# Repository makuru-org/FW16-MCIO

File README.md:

<!--
# Usecase
This is the source files needed to easily create an Framework 16 to MCIO expansion bay, so one can add a external GPU to the FW 16.
# PCB Render

# Schematics

# How to use
1. Order PCB by JLCPCB with the correct impedence matching. (pls create issue if confused or help needed)
2. Order ADT-link's MCIO to PCIe eGPU station with MCIO cable. (tested with F37C version)
3. Print repo's STD files with a 3D printer.

# License
My changes are licensed under: [https://cern-ohl.web.cern.ch/](CERN-OHL-S).

The plain PCB template is I believe the https://github.com/jyancat/ExpansionBay under CC BY 4.0.

This is a fork of the [https://github.com/Terrails/FW16-OCuLink](Terrails), work as of writting this, it is not licensed, IE under **UNLICENSED**.
--!>
# STILL IN DEV

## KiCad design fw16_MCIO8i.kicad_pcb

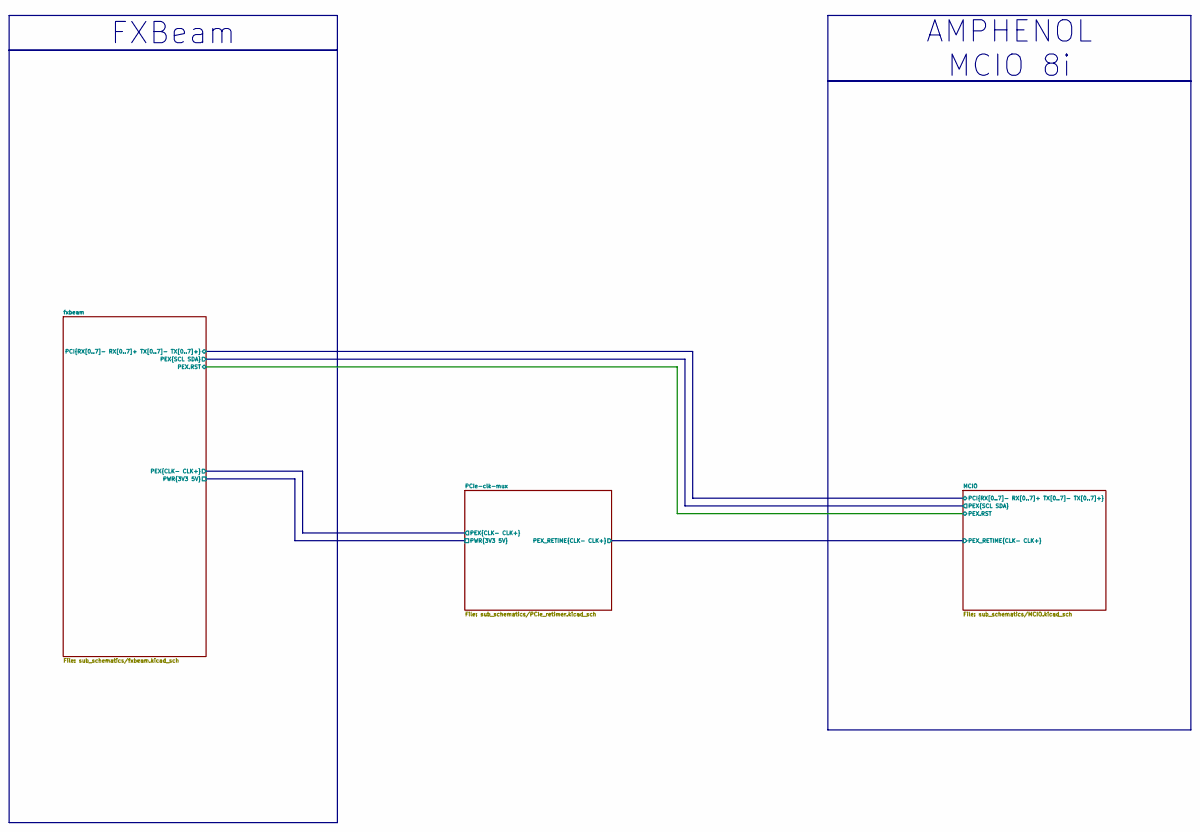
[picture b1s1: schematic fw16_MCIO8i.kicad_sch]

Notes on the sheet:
AMPHENOL MCIO 8i
FXBeam

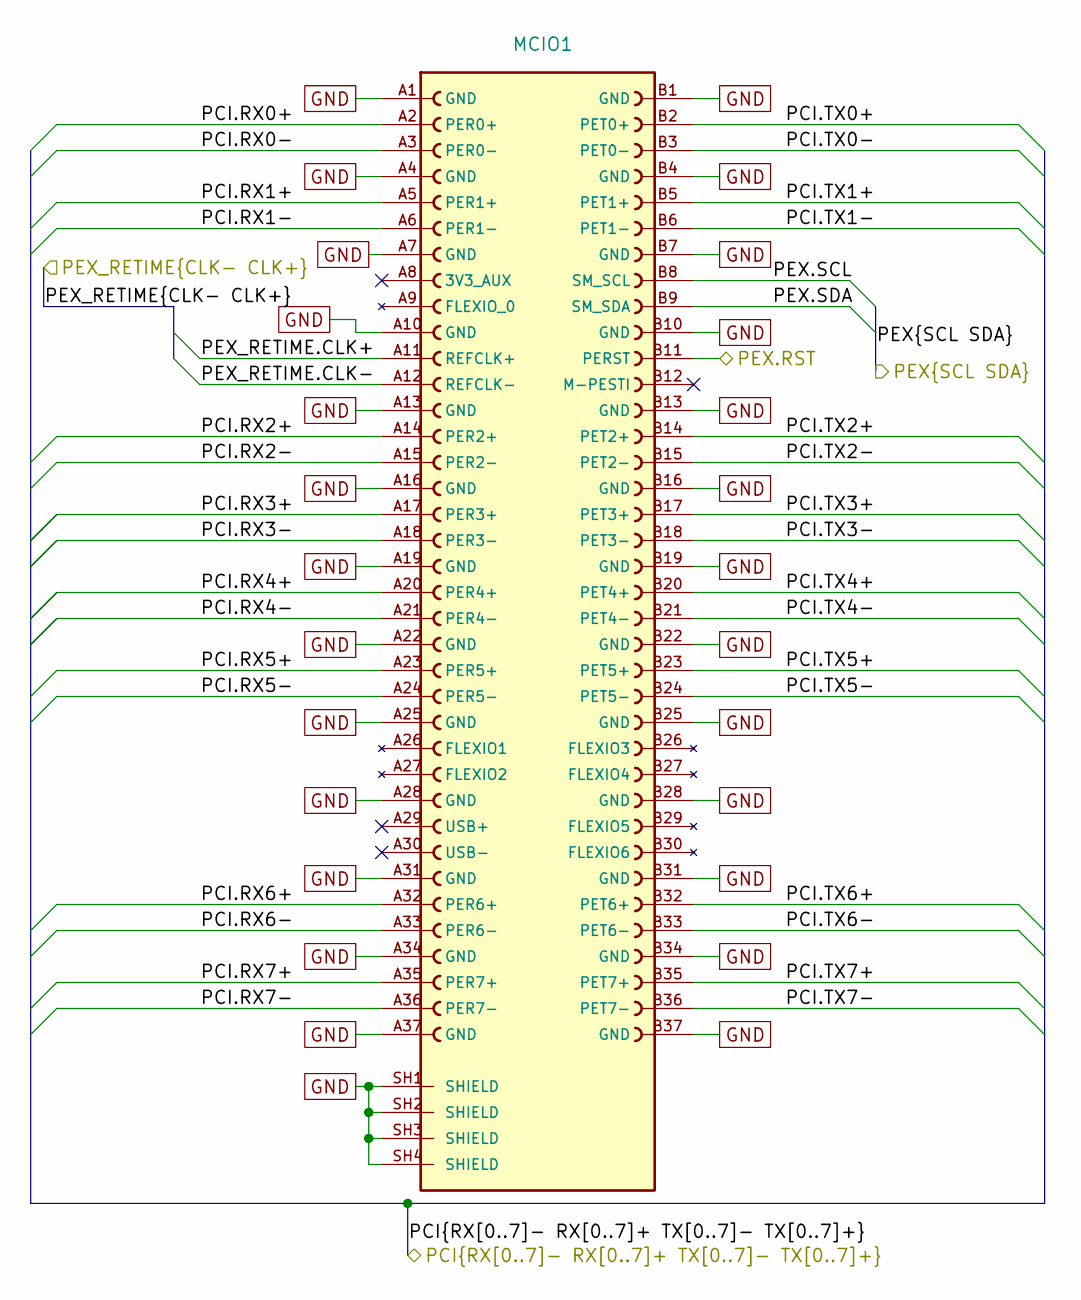
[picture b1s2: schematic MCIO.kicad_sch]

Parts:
MCIO1: G97R22312HR; AMPHENOL_G97R22312HR; PARTREV AX16; JLCPCB Part # C4499806

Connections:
/MCIO/PCI.RX0+: MCIO1.A2 (PER0+); also elsewhere on the board
/MCIO/PCI.RX0-: MCIO1.A3 (PER0-); also elsewhere on the board
/MCIO/PCI.RX1+: MCIO1.A5 (PER1+); also elsewhere on the board
/MCIO/PCI.RX1-: MCIO1.A6 (PER1-); also elsewhere on the board
/MCIO/PCI.RX2+: MCIO1.A14 (PER2+); also elsewhere on the board
/MCIO/PCI.RX2-: MCIO1.A15 (PER2-); also elsewhere on the board
/MCIO/PCI.RX3+: MCIO1.A17 (PER3+); also elsewhere on the board
/MCIO/PCI.RX3-: MCIO1.A18 (PER3-); also elsewhere on the board
/MCIO/PCI.RX4+: MCIO1.A20 (PER4+); also elsewhere on the board
/MCIO/PCI.RX4-: MCIO1.A21 (PER4-); also elsewhere on the board
/MCIO/PCI.RX5+: MCIO1.A23 (PER5+); also elsewhere on the board
/MCIO/PCI.RX5-: MCIO1.A24 (PER5-); also elsewhere on the board
/MCIO/PCI.RX6+: MCIO1.A32 (PER6+); also elsewhere on the board
/MCIO/PCI.RX6-: MCIO1.A33 (PER6-); also elsewhere on the board
/MCIO/PCI.RX7+: MCIO1.A35 (PER7+); also elsewhere on the board
/MCIO/PCI.RX7-: MCIO1.A36 (PER7-); also elsewhere on the board
/MCIO/PCI.TX0+: MCIO1.B2 (PET0+); also elsewhere on the board
/MCIO/PCI.TX0-: MCIO1.B3 (PET0-); also elsewhere on the board
/MCIO/PCI.TX1+: MCIO1.B5 (PET1+); also elsewhere on the board
/MCIO/PCI.TX1-: MCIO1.B6 (PET1-); also elsewhere on the board
/MCIO/PCI.TX2+: MCIO1.B14 (PET2+); also elsewhere on the board
/MCIO/PCI.TX2-: MCIO1.B15 (PET2-); also elsewhere on the board
/MCIO/PCI.TX3+: MCIO1.B17 (PET3+); also elsewhere on the board
/MCIO/PCI.TX3-: MCIO1.B18 (PET3-); also elsewhere on the board
/MCIO/PCI.TX4+: MCIO1.B20 (PET4+); also elsewhere on the board
/MCIO/PCI.TX4-: MCIO1.B21 (PET4-); also elsewhere on the board
/MCIO/PCI.TX5+: MCIO1.B23 (PET5+); also elsewhere on the board
/MCIO/PCI.TX5-: MCIO1.B24 (PET5-); also elsewhere on the board
/MCIO/PCI.TX6+: MCIO1.B32 (PET6+); also elsewhere on the board
/MCIO/PCI.TX6-: MCIO1.B33 (PET6-); also elsewhere on the board
/MCIO/PCI.TX7+: MCIO1.B35 (PET7+); also elsewhere on the board
/MCIO/PCI.TX7-: MCIO1.B36 (PET7-); also elsewhere on the board
/MCIO/PEX.SCL: MCIO1.B8 (SM_SCL); also elsewhere on the board
/MCIO/PEX.SDA: MCIO1.B9 (SM_SDA); also elsewhere on the board
/MCIO/PEX_RETIME.CLK+: MCIO1.A11 (REFCLK+); also elsewhere on the board
/MCIO/PEX_RETIME.CLK-: MCIO1.A12 (REFCLK-); also elsewhere on the board
/fxbeam/PEX.RST: MCIO1.B11 (PERST); also elsewhere on the board
GND: MCIO1.A1 (GND), MCIO1.A4 (GND), MCIO1.A7 (GND), MCIO1.A10 (GND), MCIO1.A13 (GND), MCIO1.A16 (GND), MCIO1.A19 (GND), MCIO1.A22 (GND), MCIO1.A25 (GND), MCIO1.A28 (GND), MCIO1.A31 (GND), MCIO1.A34 (GND), MCIO1.A37 (GND), MCIO1.B1 (GND), MCIO1.B4 (GND), MCIO1.B7 (GND), MCIO1.B10 (GND), MCIO1.B13 (GND), MCIO1.B16 (GND), MCIO1.B19 (GND), MCIO1.B22 (GND), MCIO1.B25 (GND), MCIO1.B28 (GND), MCIO1.B31 (GND), MCIO1.B34 (GND), MCIO1.B37 (GND), MCIO1.SH1 (SHIELD), MCIO1.SH2 (SHIELD), MCIO1.SH3 (SHIELD), MCIO1.SH4 (SHIELD); also elsewhere on the board

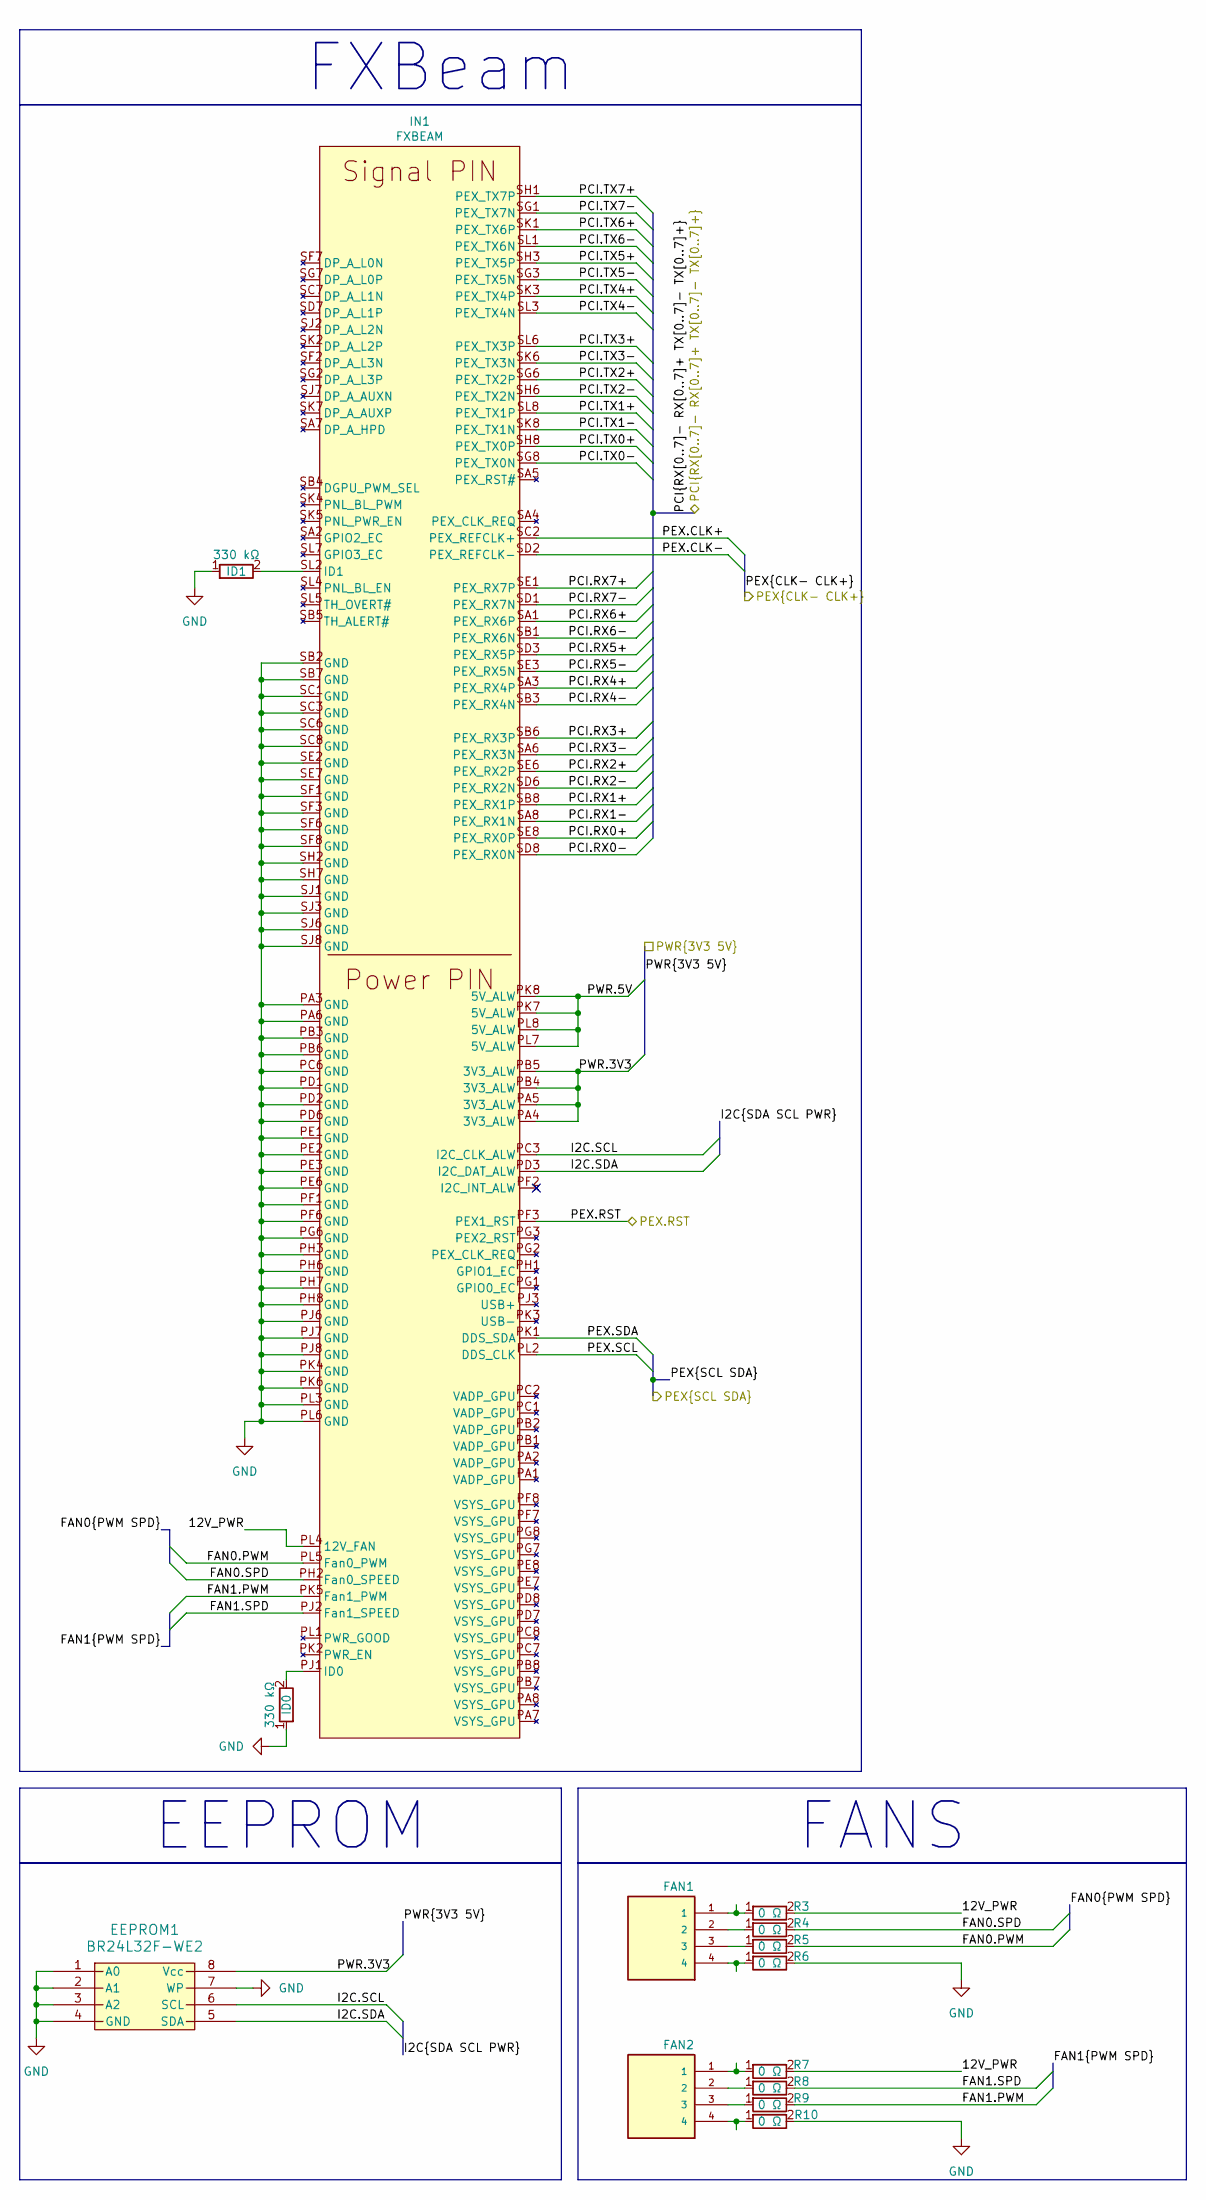
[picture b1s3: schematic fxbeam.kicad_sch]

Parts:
EEPROM1: BR24L32F-WE2; SOP8_ROM; MPN BR24L32F-WE2; JLCPCB Part # C253183
FAN1, FAN2: F3311A7H121004E200; AMPHENOL_F3311A7H121004E200; PARTREV A; JLCPCB Part # C3169422
ID0, ID1: 1206_R_560112132036; R_Wurth_WRIS-RSKS-1206_W; Part Number 560112132036; JLCPCB Part # C26798316
IN1: FXBEAM
R3, R4, R5, R6, R7, R8, R9, R10: 1206_R_560112132007; R_Wurth_WRIS-RSKS-1206_W; Part Number 560112132007; JLCPCB Part # C25268462

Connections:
/MCIO/PCI.RX0+: IN1.SE8 (PEX_RX0P); also elsewhere on the board
/MCIO/PCI.RX0-: IN1.SD8 (PEX_RX0N); also elsewhere on the board
/MCIO/PCI.RX1+: IN1.SB8 (PEX_RX1P); also elsewhere on the board
/MCIO/PCI.RX1-: IN1.SA8 (PEX_RX1N); also elsewhere on the board
/MCIO/PCI.RX2+: IN1.SE6 (PEX_RX2P); also elsewhere on the board
/MCIO/PCI.RX2-: IN1.SD6 (PEX_RX2N); also elsewhere on the board
/MCIO/PCI.RX3+: IN1.SB6 (PEX_RX3P); also elsewhere on the board
/MCIO/PCI.RX3-: IN1.SA6 (PEX_RX3N); also elsewhere on the board
/MCIO/PCI.RX4+: IN1.SA3 (PEX_RX4P); also elsewhere on the board
/MCIO/PCI.RX4-: IN1.SB3 (PEX_RX4N); also elsewhere on the board
/MCIO/PCI.RX5+: IN1.SD3 (PEX_RX5P); also elsewhere on the board
/MCIO/PCI.RX5-: IN1.SE3 (PEX_RX5N); also elsewhere on the board
/MCIO/PCI.RX6+: IN1.SA1 (PEX_RX6P); also elsewhere on the board
/MCIO/PCI.RX6-: IN1.SB1 (PEX_RX6N); also elsewhere on the board
/MCIO/PCI.RX7+: IN1.SE1 (PEX_RX7P); also elsewhere on the board
/MCIO/PCI.RX7-: IN1.SD1 (PEX_RX7N); also elsewhere on the board
/MCIO/PCI.TX0+: IN1.SH8 (PEX_TX0P); also elsewhere on the board
/MCIO/PCI.TX0-: IN1.SG8 (PEX_TX0N); also elsewhere on the board
/MCIO/PCI.TX1+: IN1.SL8 (PEX_TX1P); also elsewhere on the board
/MCIO/PCI.TX1-: IN1.SK8 (PEX_TX1N); also elsewhere on the board
/MCIO/PCI.TX2+: IN1.SG6 (PEX_TX2P); also elsewhere on the board
/MCIO/PCI.TX2-: IN1.SH6 (PEX_TX2N); also elsewhere on the board
/MCIO/PCI.TX3+: IN1.SL6 (PEX_TX3P); also elsewhere on the board
/MCIO/PCI.TX3-: IN1.SK6 (PEX_TX3N); also elsewhere on the board
/MCIO/PCI.TX4+: IN1.SK3 (PEX_TX4P); also elsewhere on the board
/MCIO/PCI.TX4-: IN1.SL3 (PEX_TX4N); also elsewhere on the board
/MCIO/PCI.TX5+: IN1.SH3 (PEX_TX5P); also elsewhere on the board
/MCIO/PCI.TX5-: IN1.SG3 (PEX_TX5N); also elsewhere on the board
/MCIO/PCI.TX6+: IN1.SK1 (PEX_TX6P); also elsewhere on the board
/MCIO/PCI.TX6-: IN1.SL1 (PEX_TX6N); also elsewhere on the board
/MCIO/PCI.TX7+: IN1.SH1 (PEX_TX7P); also elsewhere on the board
/MCIO/PCI.TX7-: IN1.SG1 (PEX_TX7N); also elsewhere on the board
/MCIO/PEX.SCL: IN1.PL2 (DDS_CLK); also elsewhere on the board
/MCIO/PEX.SDA: IN1.PK1 (DDS_SDA); also elsewhere on the board
/PCIe-clk-mux/PEX.CLK+: IN1.SC2 (PEX_REFCLK+); also elsewhere on the board
/PCIe-clk-mux/PEX.CLK-: IN1.SD2 (PEX_REFCLK-); also elsewhere on the board
/PCIe-clk-mux/PWR.3V3: EEPROM1.8 (Vcc), IN1.PA4 (3V3_ALW), IN1.PA5 (3V3_ALW), IN1.PB4 (3V3_ALW), IN1.PB5 (3V3_ALW); also elsewhere on the board
/PCIe-clk-mux/PWR.5V: IN1.PK7 (5V_ALW), IN1.PK8 (5V_ALW), IN1.PL7 (5V_ALW), IN1.PL8 (5V_ALW)
/fxbeam/12V_PWR: IN1.PL4 (12V_FAN), R3.2, R7.2
/fxbeam/FAN0.PWM: IN1.PL5 (Fan0_PWM), R5.2
/fxbeam/FAN0.SPD: IN1.PH2 (Fan0_SPEED), R4.2
/fxbeam/FAN1.PWM: IN1.PK5 (Fan1_PWM), R9.2
/fxbeam/FAN1.SPD: IN1.PJ2 (Fan1_SPEED), R8.2
/fxbeam/I2C.SCL: EEPROM1.6 (SCL), IN1.PC3 (I2C_CLK_ALW)
/fxbeam/I2C.SDA: EEPROM1.5 (SDA), IN1.PD3 (I2C_DAT_ALW)
/fxbeam/PEX.RST: IN1.PF3 (PEX1_RST); also elsewhere on the board
GND: EEPROM1.1 (A0), EEPROM1.2 (A1), EEPROM1.3 (A2), EEPROM1.4 (GND), EEPROM1.7 (WP), ID0.1, ID1.1, IN1.PA3 (GND), IN1.PA6 (GND), IN1.PB3 (GND), IN1.PB6 (GND), IN1.PC6 (GND), IN1.PD1 (GND), IN1.PD2 (GND), IN1.PD6 (GND), IN1.PE1 (GND), IN1.PE2 (GND), IN1.PE3 (GND), IN1.PE6 (GND), IN1.PF1 (GND), IN1.PF6 (GND), IN1.PG6 (GND), IN1.PH3 (GND), IN1.PH6 (GND), IN1.PH7 (GND), IN1.PH8 (GND), IN1.PJ6 (GND), IN1.PJ7 (GND), IN1.PJ8 (GND), IN1.PK4 (GND), IN1.PK6 (GND), IN1.PL3 (GND), IN1.PL6 (GND), IN1.SB2 (GND), IN1.SB7 (GND), IN1.SC1 (GND), IN1.SC3 (GND), IN1.SC6 (GND), IN1.SC8 (GND), IN1.SE2 (GND), IN1.SE7 (GND), IN1.SF1 (GND), IN1.SF3 (GND), IN1.SF6 (GND), IN1.SF8 (GND), IN1.SH2 (GND), IN1.SH7 (GND), IN1.SJ1 (GND), IN1.SJ3 (GND), IN1.SJ6 (GND), IN1.SJ8 (GND), R6.2, R10.2; also elsewhere on the board
unnamed: FAN1.1, R3.1
unnamed: FAN1.2, R4.1
unnamed: FAN1.3, R5.1
unnamed: FAN1.4, R6.1
unnamed: FAN2.1, R7.1
unnamed: FAN2.2, R8.1
unnamed: FAN2.3, R9.1
unnamed: FAN2.4, R10.1
unnamed: ID0.2, IN1.PJ1 (ID0)
unnamed: ID1.2, IN1.SL2 (ID1)

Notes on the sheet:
EEPROM
FANS
FXBeam

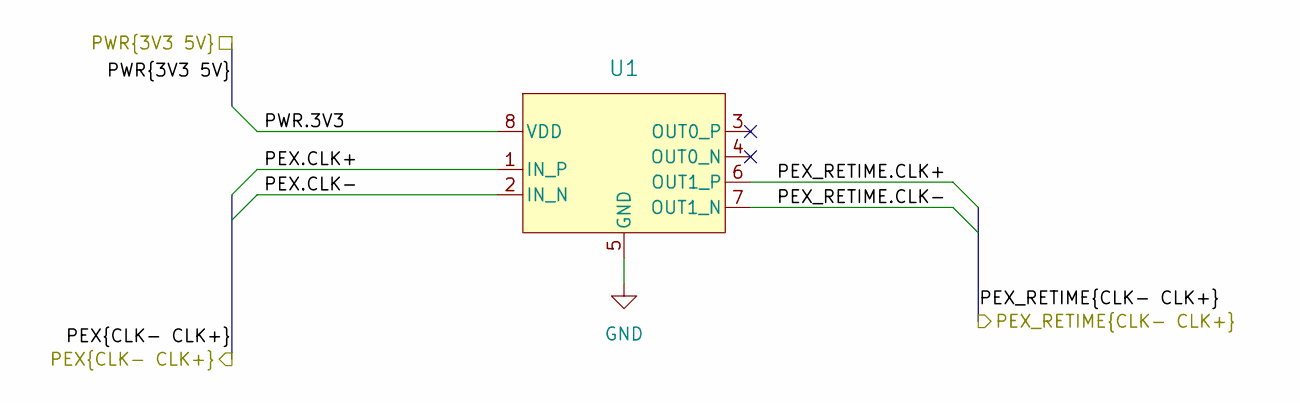
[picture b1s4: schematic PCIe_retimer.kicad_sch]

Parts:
U1: SY75602ATWL-TR; VDFN8_NNC_MCH; MPN SY75602ATWL-TR; JLCPCB Part # C3613417

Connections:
/MCIO/PEX_RETIME.CLK+: U1.6 (OUT1_P); also elsewhere on the board
/MCIO/PEX_RETIME.CLK-: U1.7 (OUT1_N); also elsewhere on the board
/PCIe-clk-mux/PEX.CLK+: U1.1 (IN_P); also elsewhere on the board
/PCIe-clk-mux/PEX.CLK-: U1.2 (IN_N); also elsewhere on the board
/PCIe-clk-mux/PWR.3V3: U1.8 (VDD); also elsewhere on the board
GND: U1.5 (GND); also elsewhere on the board

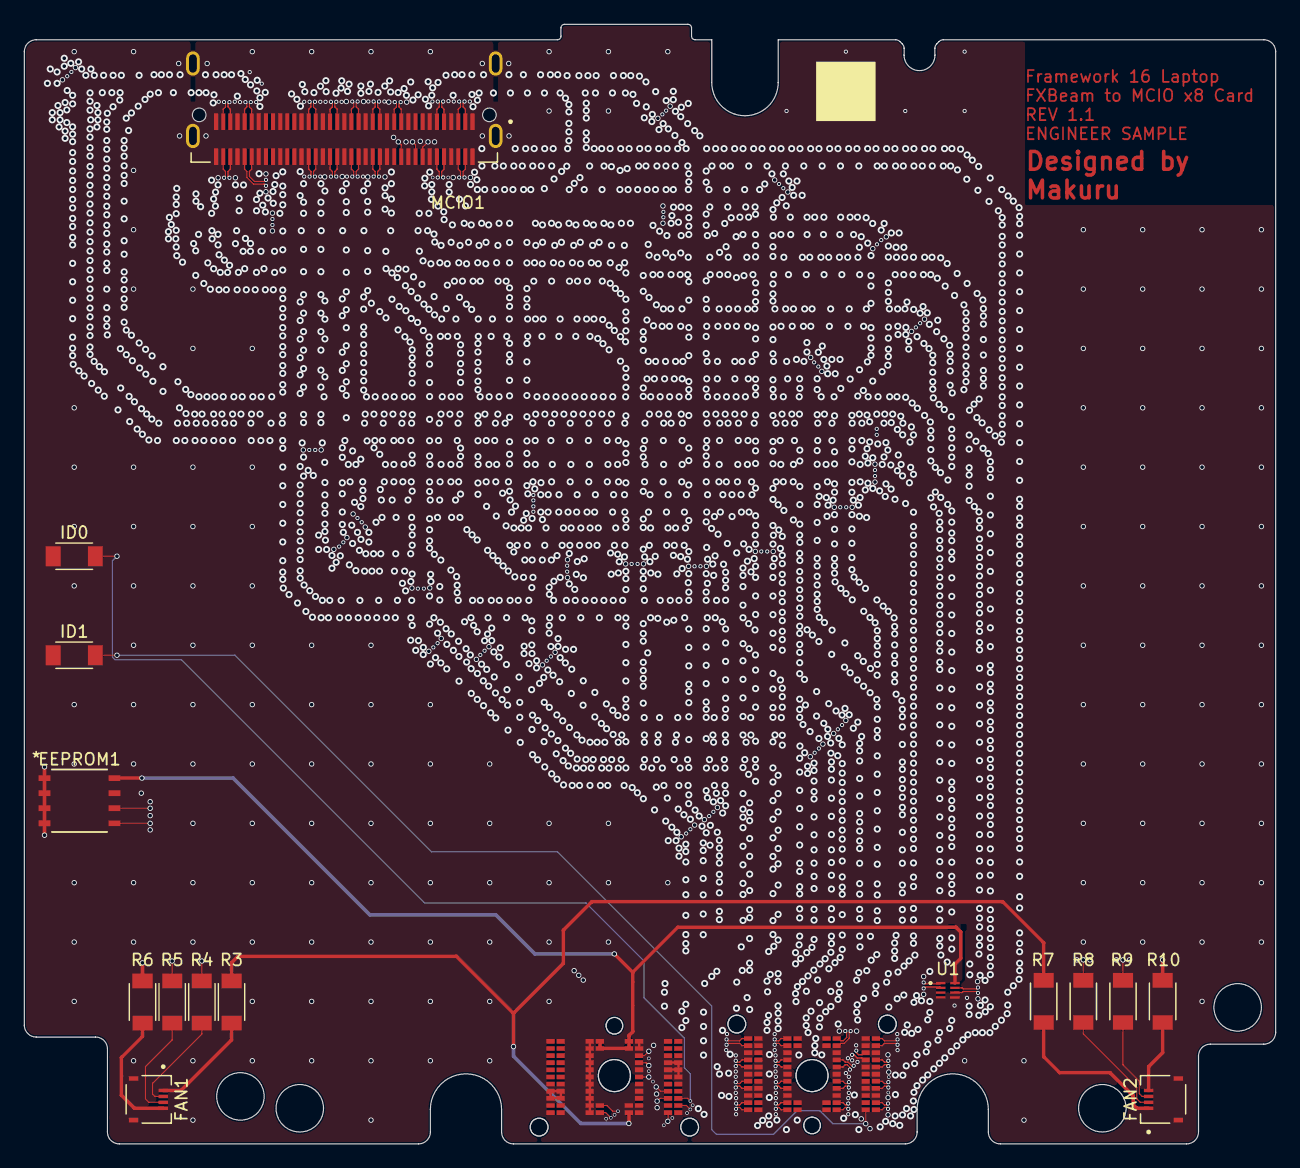
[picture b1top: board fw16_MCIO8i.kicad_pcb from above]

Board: 6 copper layers, 105.4 x 94.3 mm, 16 parts (0 on the bottom side), 59 nets.

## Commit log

2025-12-07 Renamed project
2025-12-07 Imported MCIO connector
2025-12-07 Connected MCIO on Schematics
2025-12-07 Imported PCIe Redriver
2025-12-07 Changed naming to lowercase
2025-12-08 New fan connector
2025-12-09 Cleanup
2025-12-12 Switched redriver
2025-12-12 added Oculink part
2025-12-14 Fixups
2025-12-16 changed parts
2025-12-18 Rerouted fxbeam
2025-12-19 routed
2025-12-19 Fixed errors
2025-12-23 New routing
2025-12-23 Deleted old images.
2026-01-02 Removed pour on signal layers
2026-01-22 diodes and jumpers
2026-01-22 README and cleanup
2026-01-23 Skewing around
2026-01-26 MPN added and removed unedded diode
2026-01-27 Switched capacitor
2026-02-08 Fixed skew and silkscreen
2026-02-09 MPN & LCSC
2026-03-01 Order
2026-03-15 Fixed EEPROM error
2026-03-28 Schematics fixed
2026-03-28 Switched to large board
2026-04-01 PCIe redriver and buck converter
2026-04-02 Schematics revamped
2026-04-06 moved schematics
2026-04-07 buck converter changes
2026-04-08 buck converter
2026-04-09 buck converter component
2026-04-14 Added Inductors
2026-04-14 Added resistors
2026-04-14 Added capacitors
2026-04-15 Fixed typo
2026-04-15 Moved to big inductor
2026-04-15 Working buck converter
2026-04-15 Footprint
2026-04-17 changed 1.8V buck
2026-04-19 Buck closer to recommended value
2026-04-19 PCIe shematic fix
2026-05-15 Switch to retimer for only clock
2026-05-15 Fixed board dimensions
2026-05-16 Fixed board stackup
2026-05-17 Routing
2026-05-17 Routing small schematic fix
2026-05-18 Preparing order
2026-05-18 adjusted cut layer
2026-05-18 Skew
2026-05-19 changed impedence matching
2026-05-30 Smothing
2026-05-30 Order prepare
2026-06-01 Order rev1.1
2026-06-24 Reskew changed skematics
2026-06-25 updated kicad oot
2026-06-25 Via fencing
2026-06-25 schematics fixup
